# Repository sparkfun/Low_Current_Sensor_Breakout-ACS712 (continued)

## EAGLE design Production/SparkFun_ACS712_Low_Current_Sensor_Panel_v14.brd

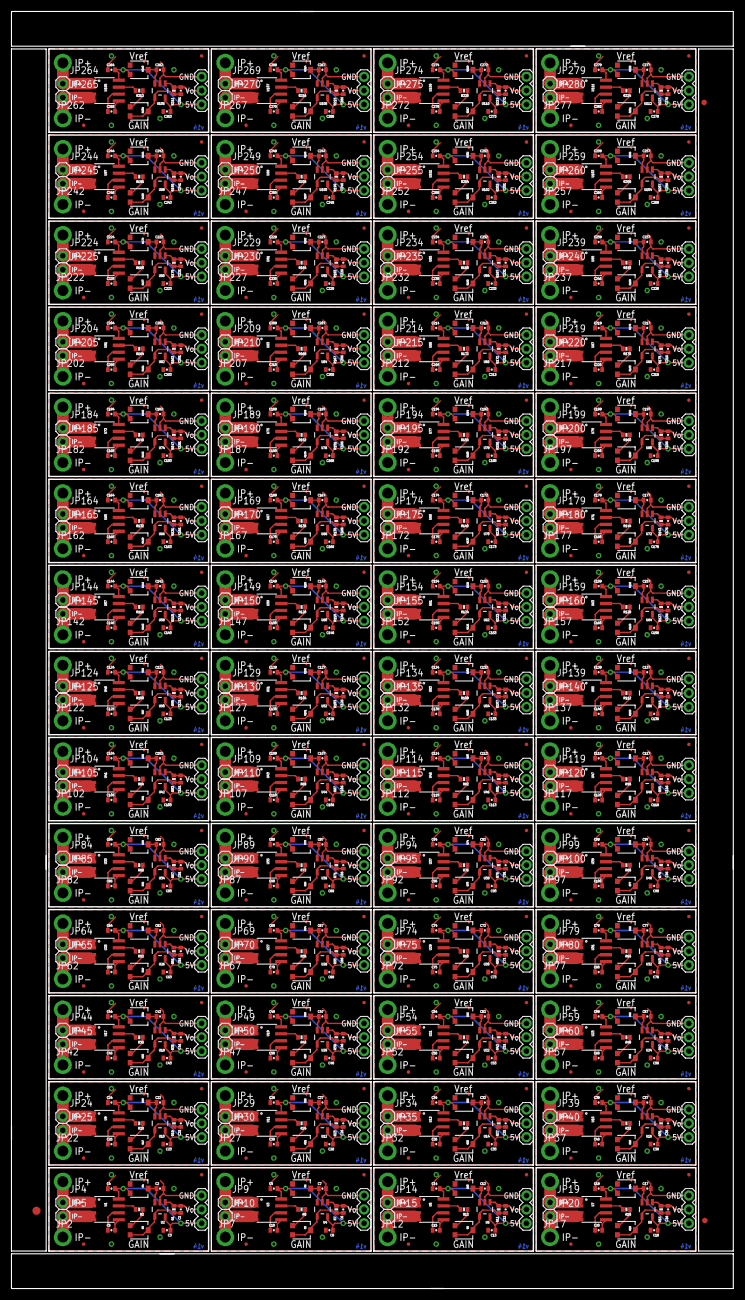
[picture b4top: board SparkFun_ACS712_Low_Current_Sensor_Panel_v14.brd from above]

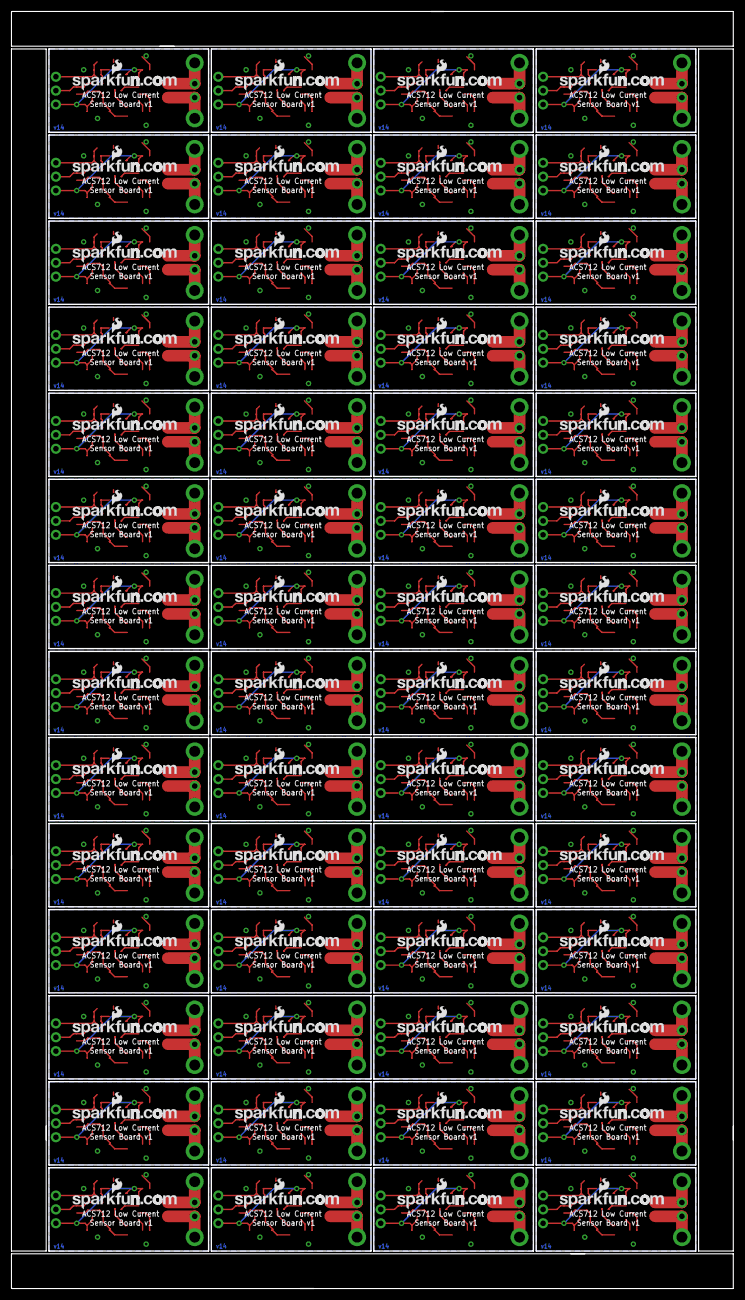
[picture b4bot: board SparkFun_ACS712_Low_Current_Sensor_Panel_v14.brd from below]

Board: 2 copper layers, 132.0 x 233.6 mm, 1067 parts (56 on the bottom side), 560 nets.

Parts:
C1, C2, C3, C4, C6, C7, C8, C9, C11, C12, C13, C14, C16, C17, C18, C19, C21, C22, C23, C24, C26, C27, C28, C29, C31, C32, C33, C34, C36, C37, C38, C39, C41, C42, C43, C44, C46, C47, C48, C49, C51, C52, C53, C54, C56, C57, C58, C59, C61, C62, C63, C64, C66, C67, C68, C69, C71, C72, C73, C74, C76, C77, C78, C79, C81, C82, C83, C84, C86, C87, C88, C89, C91, C92, C93, C94, C96, C97, C98, C99, C101, C102, C103, C104, C106, C107, C108, C109, C111, C112, C113, C114, C116, C117, C118, C119, C121, C122, C123, C124, C126, C127, C128, C129, C131, C132, C133, C134, C136, C137, C138, C139, C141, C142, C143, C144, C146, C147, C148, C149, C151, C152, C153, C154, C156, C157, C158, C159, C161, C162, C163, C164, C166, C167, C168, C169, C171, C172, C173, C174, C176, C177, C178, C179, C181, C182, C183, C184, C186, C187, C188, C189, C191, C192, C193, C194, C196, C197, C198, C199, C201, C202, C203, C204, C206, C207, C208, C209, C211, C212, C213, C214, C216, C217, C218, C219, C221, C222, C223, C224, C226, C227, C228, C229, C231, C232, C233, C234, C236, C237, C238, C239, C241, C242, C243, C244, C246, C247, C248, C249, C251, C252, C253, C254, C256, C257, C258, C259, C261, C262, C263, C264, C266, C267, C268, C269, C271, C272, C273, C274, C276, C277, C278, C279: 0.1uF; 0402-CAP
C5, C10, C15, C20, C25, C30, C35, C40, C45, C50, C55, C60, C65, C70, C75, C80, C85, C90, C95, C100, C105, C110, C115, C120, C125, C130, C135, C140, C145, C150, C155, C160, C165, C170, C175, C180, C185, C190, C195, C200, C205, C210, C215, C220, C225, C230, C235, C240, C245, C250, C255, C260, C265, C270, C275, C280: 1nF; 0402-CAP
E$1: FIDUCIAL-1.5X3
E$5, E$7: FIDUCIAL-1X2
JP1, JP2, JP6, JP7, JP11, JP12, JP16, JP17, JP21, JP22, JP26, JP27, JP31, JP32, JP36, JP37, JP41, JP42, JP46, JP47, JP51, JP52, JP56, JP57, JP61, JP62, JP66, JP67, JP71, JP72, JP76, JP77, JP81, JP82, JP86, JP87, JP91, JP92, JP96, JP97, JP101, JP102, JP106, JP107, JP111, JP112, JP116, JP117, JP121, JP122, JP126, JP127, JP131, JP132, JP136, JP137, JP141, JP142, JP146, JP147, JP151, JP152, JP156, JP157, JP161, JP162, JP166, JP167, JP171, JP172, JP176, JP177, JP181, JP182, JP186, JP187, JP191, JP192, JP196, JP197, JP201, JP202, JP206, JP207, JP211, JP212, JP216, JP217, JP221, JP222, JP226, JP227, JP231, JP232, JP236, JP237, JP241, JP242, JP246, JP247, JP251, JP252, JP256, JP257, JP261, JP262, JP266, JP267, JP271, JP272, JP276, JP277: M01PTH_2MM; 1X01_2MM
JP3, JP8, JP13, JP18, JP23, JP28, JP33, JP38, JP43, JP48, JP53, JP58, JP63, JP68, JP73, JP78, JP83, JP88, JP93, JP98, JP103, JP108, JP113, JP118, JP123, JP128, JP133, JP138, JP143, JP148, JP153, JP158, JP163, JP168, JP173, JP178, JP183, JP188, JP193, JP198, JP203, JP208, JP213, JP218, JP223, JP228, JP233, JP238, JP243, JP248, JP253, JP258, JP263, JP268, JP273, JP278: 1X03
JP4, JP5, JP9, JP10, JP14, JP15, JP19, JP20, JP24, JP25, JP29, JP30, JP34, JP35, JP39, JP40, JP44, JP45, JP49, JP50, JP54, JP55, JP59, JP60, JP64, JP65, JP69, JP70, JP74, JP75, JP79, JP80, JP84, JP85, JP89, JP90, JP94, JP95, JP99, JP100, JP104, JP105, JP109, JP110, JP114, JP115, JP119, JP120, JP124, JP125, JP129, JP130, JP134, JP135, JP139, JP140, JP144, JP145, JP149, JP150, JP154, JP155, JP159, JP160, JP164, JP165, JP169, JP170, JP174, JP175, JP179, JP180, JP184, JP185, JP189, JP190, JP194, JP195, JP199, JP200, JP204, JP205, JP209, JP210, JP214, JP215, JP219, JP220, JP224, JP225, JP229, JP230, JP234, JP235, JP239, JP240, JP244, JP245, JP249, JP250, JP254, JP255, JP259, JP260, JP264, JP265, JP269, JP270, JP274, JP275, JP279, JP280: M01PTH; 1X01
R1, R7, R11, R15, R19, R23, R27, R31, R35, R39, R43, R47, R51, R55, R59, R63, R67, R71, R75, R79, R83, R87, R91, R95, R99, R103, R107, R111, R115, R119, R123, R127, R131, R135, R139, R143, R147, R151, R155, R159, R163, R167, R171, R175, R179, R183, R187, R191, R195, R199, R203, R207, R211, R215, R219, R223: 47K; 0402-RES
R2, R8, R12, R16, R20, R24, R28, R32, R36, R40, R44, R48, R52, R56, R60, R64, R68, R72, R76, R80, R84, R88, R92, R96, R100, R104, R108, R112, R116, R120, R124, R128, R132, R136, R140, R144, R148, R152, R156, R160, R164, R168, R172, R176, R180, R184, R188, R192, R196, R200, R204, R208, R212, R216, R220, R224: 1K; 0402-RES
R3, R4, R5, R6, R9, R10, R13, R14, R17, R18, R21, R22, R25, R26, R29, R30, R33, R34, R37, R38, R41, R42, R45, R46, R49, R50, R53, R54, R57, R58, R61, R62, R65, R66, R69, R70, R73, R74, R77, R78, R81, R82, R85, R86, R89, R90, R93, R94, R97, R98, R101, R102, R105, R106, R109, R110, R113, R114, R117, R118, R121, R122, R125, R126, R129, R130, R133, R134, R137, R138, R141, R142, R145, R146, R149, R150, R153, R154, R157, R158, R161, R162, R165, R166, R169, R170, R173, R174, R177, R178, R181, R182, R185, R186, R189, R190, R193, R194, R197, R198, R201, R202, R205, R206, R209, R210, R213, R214, R217, R218, R221, R222: TRIMPOTSMD; TRIMPOT-3MM
U1, U3, U5, U7, U9, U11, U13, U15, U17, U19, U21, U23, U25, U27, U29, U31, U33, U35, U37, U39, U41, U43, U45, U47, U49, U51, U53, U55, U57, U59, U61, U63, U65, U67, U69, U71, U73, U75, U77, U79, U81, U83, U85, U87, U89, U91, U93, U95, U97, U99, U101, U103, U105, U107, U109, U111: ACS712; SO08
U2, U4, U6, U8, U10, U12, U14, U16, U18, U20, U22, U24, U26, U28, U30, U32, U34, U36, U38, U40, U42, U44, U46, U48, U50, U52, U54, U56, U58, U60, U62, U64, U66, U68, U70, U72, U74, U76, U78, U80, U82, U84, U86, U88, U90, U92, U94, U96, U98, U100, U102, U104, U106, U108, U110, U112: OPA344; SOT23-5
U$1, U$3, U$5, U$6, U$8, U$9, U$11, U$12, U$14, U$15, U$17, U$18, U$20, U$21, U$23, U$24, U$26, U$27, U$29, U$30, U$32, U$33, U$35, U$36, U$38, U$39, U$41, U$42, U$44, U$45, U$47, U$48, U$50, U$51, U$53, U$54, U$56, U$57, U$59, U$60, U$62, U$63, U$65, U$66, U$68, U$69, U$71, U$72, U$74, U$75, U$77, U$78, U$80, U$81, U$83, U$84, U$86, U$87, U$89, U$90, U$92, U$93, U$95, U$96, U$98, U$99, U$101, U$102, U$104, U$105, U$107, U$108, U$110, U$111, U$113, U$114, U$116, U$117, U$119, U$120, U$122, U$123, U$125, U$126, U$128, U$129, U$131, U$132, U$134, U$135, U$137, U$138, U$140, U$141, U$143, U$144, U$146, U$147, U$149, U$150, U$152, U$153, U$155, U$156, U$158, U$159, U$161, U$162, U$164, U$165, U$167, U$168: FIDUCIALUFIDUCIAL; MICRO-FIDUCIAL
U$2, U$4, U$7, U$10, U$13, U$16, U$19, U$22, U$25, U$28, U$31, U$34, U$37, U$40, U$43, U$46, U$49, U$52, U$55, U$58, U$61, U$64, U$67, U$70, U$73, U$76, U$79, U$82, U$85, U$88, U$91, U$94, U$97, U$100, U$103, U$106, U$109, U$112, U$115, U$118, U$121, U$124, U$127, U$130, U$133, U$136, U$139, U$142, U$145, U$148, U$151, U$154, U$157, U$160, U$163, U$166: LOGO-SFENEW; SFE-NEW-WEBLOGO

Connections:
5V: C3.1, C4.2, JP3.1, R4.3, U1.8, U2.5
5V1: C8.1, C9.2, JP8.1, R6.3, U3.8, U4.5
5V2: C13.1, C14.2, JP13.1, R10.3, U5.8, U6.5
5V3: C18.1, C19.2, JP18.1, R14.3, U7.8, U8.5
5V4: C23.1, C24.2, JP23.1, R18.3, U9.8, U10.5
5V5: C28.1, C29.2, JP28.1, R22.3, U11.8, U12.5
5V6: C33.1, C34.2, JP33.1, R26.3, U13.8, U14.5
5V7: C38.1, C39.2, JP38.1, R30.3, U15.8, U16.5
5V8: C43.1, C44.2, JP43.1, R34.3, U17.8, U18.5
5V9: C48.1, C49.2, JP48.1, R38.3, U19.8, U20.5
5V10: C53.1, C54.2, JP53.1, R42.3, U21.8, U22.5
5V11: C58.1, C59.2, JP58.1, R46.3, U23.8, U24.5
5V12: C63.1, C64.2, JP63.1, R50.3, U25.8, U26.5
5V13: C68.1, C69.2, JP68.1, R54.3, U27.8, U28.5
5V14: C73.1, C74.2, JP73.1, R58.3, U29.8, U30.5
5V15: C78.1, C79.2, JP78.1, R62.3, U31.8, U32.5
5V16: C83.1, C84.2, JP83.1, R66.3, U33.8, U34.5
5V17: C88.1, C89.2, JP88.1, R70.3, U35.8, U36.5
5V18: C93.1, C94.2, JP93.1, R74.3, U37.8, U38.5
5V19: C98.1, C99.2, JP98.1, R78.3, U39.8, U40.5
5V20: C103.1, C104.2, JP103.1, R82.3, U41.8, U42.5
5V21: C108.1, C109.2, JP108.1, R86.3, U43.8, U44.5
5V22: C113.1, C114.2, JP113.1, R90.3, U45.8, U46.5
5V23: C118.1, C119.2, JP118.1, R94.3, U47.8, U48.5
5V24: C123.1, C124.2, JP123.1, R98.3, U49.8, U50.5
5V25: C128.1, C129.2, JP128.1, R102.3, U51.8, U52.5
5V26: C133.1, C134.2, JP133.1, R106.3, U53.8, U54.5
5V27: C138.1, C139.2, JP138.1, R110.3, U55.8, U56.5
5V28: C143.1, C144.2, JP143.1, R114.3, U57.8, U58.5
5V29: C148.1, C149.2, JP148.1, R118.3, U59.8, U60.5
5V30: C153.1, C154.2, JP153.1, R122.3, U61.8, U62.5
5V31: C158.1, C159.2, JP158.1, R126.3, U63.8, U64.5
5V32: C163.1, C164.2, JP163.1, R130.3, U65.8, U66.5
5V33: C168.1, C169.2, JP168.1, R134.3, U67.8, U68.5
5V34: C173.1, C174.2, JP173.1, R138.3, U69.8, U70.5
5V35: C178.1, C179.2, JP178.1, R142.3, U71.8, U72.5
5V36: C183.1, C184.2, JP183.1, R146.3, U73.8, U74.5
5V37: C188.1, C189.2, JP188.1, R150.3, U75.8, U76.5
5V38: C193.1, C194.2, JP193.1, R154.3, U77.8, U78.5
5V39: C198.1, C199.2, JP198.1, R158.3, U79.8, U80.5
5V40: C203.1, C204.2, JP203.1, R162.3, U81.8, U82.5
5V41: C208.1, C209.2, JP208.1, R166.3, U83.8, U84.5
5V42: C213.1, C214.2, JP213.1, R170.3, U85.8, U86.5
5V43: C218.1, C219.2, JP218.1, R174.3, U87.8, U88.5
5V44: C223.1, C224.2, JP223.1, R178.3, U89.8, U90.5
5V45: C228.1, C229.2, JP228.1, R182.3, U91.8, U92.5
5V46: C233.1, C234.2, JP233.1, R186.3, U93.8, U94.5
5V47: C238.1, C239.2, JP238.1, R190.3, U95.8, U96.5
5V48: C243.1, C244.2, JP243.1, R194.3, U97.8, U98.5
5V49: C248.1, C249.2, JP248.1, R198.3, U99.8, U100.5
5V50: C253.1, C254.2, JP253.1, R202.3, U101.8, U102.5
5V51: C258.1, C259.2, JP258.1, R206.3, U103.8, U104.5
5V52: C263.1, C264.2, JP263.1, R210.3, U105.8, U106.5
5V53: C268.1, C269.2, JP268.1, R214.3, U107.8, U108.5
5V54: C273.1, C274.2, JP273.1, R218.3, U109.8, U110.5
5V55: C278.1, C279.2, JP278.1, R222.3, U111.8, U112.5
GND: C2.2, C3.2, C4.1, C5.2, JP3.3, R4.1, U1.5, U2.2
GND1: C7.2, C8.2, C9.1, C10.2, JP8.3, R6.1, U3.5, U4.2
GND2: C12.2, C13.2, C14.1, C15.2, JP13.3, R10.1, U5.5, U6.2
GND3: C17.2, C18.2, C19.1, C20.2, JP18.3, R14.1, U7.5, U8.2
GND4: C22.2, C23.2, C24.1, C25.2, JP23.3, R18.1, U9.5, U10.2
GND5: C27.2, C28.2, C29.1, C30.2, JP28.3, R22.1, U11.5, U12.2
GND6: C32.2, C33.2, C34.1, C35.2, JP33.3, R26.1, U13.5, U14.2
GND7: C37.2, C38.2, C39.1, C40.2, JP38.3, R30.1, U15.5, U16.2
GND8: C42.2, C43.2, C44.1, C45.2, JP43.3, R34.1, U17.5, U18.2
GND9: C47.2, C48.2, C49.1, C50.2, JP48.3, R38.1, U19.5, U20.2
GND10: C52.2, C53.2, C54.1, C55.2, JP53.3, R42.1, U21.5, U22.2
GND11: C57.2, C58.2, C59.1, C60.2, JP58.3, R46.1, U23.5, U24.2
GND12: C62.2, C63.2, C64.1, C65.2, JP63.3, R50.1, U25.5, U26.2
GND13: C67.2, C68.2, C69.1, C70.2, JP68.3, R54.1, U27.5, U28.2
GND14: C72.2, C73.2, C74.1, C75.2, JP73.3, R58.1, U29.5, U30.2
GND15: C77.2, C78.2, C79.1, C80.2, JP78.3, R62.1, U31.5, U32.2
GND16: C82.2, C83.2, C84.1, C85.2, JP83.3, R66.1, U33.5, U34.2
GND17: C87.2, C88.2, C89.1, C90.2, JP88.3, R70.1, U35.5, U36.2
GND18: C92.2, C93.2, C94.1, C95.2, JP93.3, R74.1, U37.5, U38.2
GND19: C97.2, C98.2, C99.1, C100.2, JP98.3, R78.1, U39.5, U40.2
GND20: C102.2, C103.2, C104.1, C105.2, JP103.3, R82.1, U41.5, U42.2
GND21: C107.2, C108.2, C109.1, C110.2, JP108.3, R86.1, U43.5, U44.2
GND22: C112.2, C113.2, C114.1, C115.2, JP113.3, R90.1, U45.5, U46.2
GND23: C117.2, C118.2, C119.1, C120.2, JP118.3, R94.1, U47.5, U48.2
GND24: C122.2, C123.2, C124.1, C125.2, JP123.3, R98.1, U49.5, U50.2
GND25: C127.2, C128.2, C129.1, C130.2, JP128.3, R102.1, U51.5, U52.2
GND26: C132.2, C133.2, C134.1, C135.2, JP133.3, R106.1, U53.5, U54.2
GND27: C137.2, C138.2, C139.1, C140.2, JP138.3, R110.1, U55.5, U56.2
GND28: C142.2, C143.2, C144.1, C145.2, JP143.3, R114.1, U57.5, U58.2
GND29: C147.2, C148.2, C149.1, C150.2, JP148.3, R118.1, U59.5, U60.2
GND30: C152.2, C153.2, C154.1, C155.2, JP153.3, R122.1, U61.5, U62.2
GND31: C157.2, C158.2, C159.1, C160.2, JP158.3, R126.1, U63.5, U64.2
GND32: C162.2, C163.2, C164.1, C165.2, JP163.3, R130.1, U65.5, U66.2
GND33: C167.2, C168.2, C169.1, C170.2, JP168.3, R134.1, U67.5, U68.2
GND34: C172.2, C173.2, C174.1, C175.2, JP173.3, R138.1, U69.5, U70.2
GND35: C177.2, C178.2, C179.1, C180.2, JP178.3, R142.1, U71.5, U72.2
GND36: C182.2, C183.2, C184.1, C185.2, JP183.3, R146.1, U73.5, U74.2
GND37: C187.2, C188.2, C189.1, C190.2, JP188.3, R150.1, U75.5, U76.2
GND38: C192.2, C193.2, C194.1, C195.2, JP193.3, R154.1, U77.5, U78.2
GND39: C197.2, C198.2, C199.1, C200.2, JP198.3, R158.1, U79.5, U80.2
GND40: C202.2, C203.2, C204.1, C205.2, JP203.3, R162.1, U81.5, U82.2
GND41: C207.2, C208.2, C209.1, C210.2, JP208.3, R166.1, U83.5, U84.2
GND42: C212.2, C213.2, C214.1, C215.2, JP213.3, R170.1, U85.5, U86.2
GND43: C217.2, C218.2, C219.1, C220.2, JP218.3, R174.1, U87.5, U88.2
GND44: C222.2, C223.2, C224.1, C225.2, JP223.3, R178.1, U89.5, U90.2
GND45: C227.2, C228.2, C229.1, C230.2, JP228.3, R182.1, U91.5, U92.2
GND46: C232.2, C233.2, C234.1, C235.2, JP233.3, R186.1, U93.5, U94.2
GND47: C237.2, C238.2, C239.1, C240.2, JP238.3, R190.1, U95.5, U96.2
GND48: C242.2, C243.2, C244.1, C245.2, JP243.3, R194.1, U97.5, U98.2
GND49: C247.2, C248.2, C249.1, C250.2, JP248.3, R198.1, U99.5, U100.2
GND50: C252.2, C253.2, C254.1, C255.2, JP253.3, R202.1, U101.5, U102.2
GND51: C257.2, C258.2, C259.1, C260.2, JP258.3, R206.1, U103.5, U104.2
GND52: C262.2, C263.2, C264.1, C265.2, JP263.3, R210.1, U105.5, U106.2
GND53: C267.2, C268.2, C269.1, C270.2, JP268.3, R214.1, U107.5, U108.2
GND54: C272.2, C273.2, C274.1, C275.2, JP273.3, R218.1, U109.5, U110.2
GND55: C277.2, C278.2, C279.1, C280.2, JP278.3, R222.1, U111.5, U112.2
IP+: JP1.1, JP4.1, U1.1, U1.2
IP+1: JP6.1, JP9.1, U3.1, U3.2
IP+2: JP11.1, JP14.1, U5.1, U5.2
IP+3: JP16.1, JP19.1, U7.1, U7.2
IP+4: JP21.1, JP24.1, U9.1, U9.2
IP+5: JP26.1, JP29.1, U11.1, U11.2
IP+6: JP31.1, JP34.1, U13.1, U13.2
IP+7: JP36.1, JP39.1, U15.1, U15.2
IP+8: JP41.1, JP44.1, U17.1, U17.2
IP+9: JP46.1, JP49.1, U19.1, U19.2
IP+10: JP51.1, JP54.1, U21.1, U21.2
IP+11: JP56.1, JP59.1, U23.1, U23.2
IP+12: JP61.1, JP64.1, U25.1, U25.2
IP+13: JP66.1, JP69.1, U27.1, U27.2
IP+14: JP71.1, JP74.1, U29.1, U29.2
IP+15: JP76.1, JP79.1, U31.1, U31.2
IP+16: JP81.1, JP84.1, U33.1, U33.2
IP+17: JP86.1, JP89.1, U35.1, U35.2
IP+18: JP91.1, JP94.1, U37.1, U37.2
IP+19: JP96.1, JP99.1, U39.1, U39.2
IP+20: JP101.1, JP104.1, U41.1, U41.2
IP+21: JP106.1, JP109.1, U43.1, U43.2
IP+22: JP111.1, JP114.1, U45.1, U45.2
IP+23: JP116.1, JP119.1, U47.1, U47.2
IP+24: JP121.1, JP124.1, U49.1, U49.2
IP+25: JP126.1, JP129.1, U51.1, U51.2
IP+26: JP131.1, JP134.1, U53.1, U53.2
IP+27: JP136.1, JP139.1, U55.1, U55.2
IP+28: JP141.1, JP144.1, U57.1, U57.2
IP+29: JP146.1, JP149.1, U59.1, U59.2
IP+30: JP151.1, JP154.1, U61.1, U61.2
IP+31: JP156.1, JP159.1, U63.1, U63.2
IP+32: JP161.1, JP164.1, U65.1, U65.2
IP+33: JP166.1, JP169.1, U67.1, U67.2
IP+34: JP171.1, JP174.1, U69.1, U69.2
IP+35: JP176.1, JP179.1, U71.1, U71.2
IP+36: JP181.1, JP184.1, U73.1, U73.2
IP+37: JP186.1, JP189.1, U75.1, U75.2
IP+38: JP191.1, JP194.1, U77.1, U77.2
IP+39: JP196.1, JP199.1, U79.1, U79.2
IP+40: JP201.1, JP204.1, U81.1, U81.2
IP+41: JP206.1, JP209.1, U83.1, U83.2
IP+42: JP211.1, JP214.1, U85.1, U85.2
IP+43: JP216.1, JP219.1, U87.1, U87.2
IP+44: JP221.1, JP224.1, U89.1, U89.2
IP+45: JP226.1, JP229.1, U91.1, U91.2
IP+46: JP231.1, JP234.1, U93.1, U93.2
IP+47: JP236.1, JP239.1, U95.1, U95.2
IP+48: JP241.1, JP244.1, U97.1, U97.2
IP+49: JP246.1, JP249.1, U99.1, U99.2
IP+50: JP251.1, JP254.1, U101.1, U101.2
IP+51: JP256.1, JP259.1, U103.1, U103.2
IP+52: JP261.1, JP264.1, U105.1, U105.2
IP+53: JP266.1, JP269.1, U107.1, U107.2
IP+54: JP271.1, JP274.1, U109.1, U109.2
IP+55: JP276.1, JP279.1, U111.1, U111.2
IP-: JP2.1, JP5.1, U1.3, U1.4
IP-1: JP7.1, JP10.1, U3.3, U3.4
IP-2: JP12.1, JP15.1, U5.3, U5.4
IP-3: JP17.1, JP20.1, U7.3, U7.4
IP-4: JP22.1, JP25.1, U9.3, U9.4
IP-5: JP27.1, JP30.1, U11.3, U11.4
IP-6: JP32.1, JP35.1, U13.3, U13.4
IP-7: JP37.1, JP40.1, U15.3, U15.4
IP-8: JP42.1, JP45.1, U17.3, U17.4
IP-9: JP47.1, JP50.1, U19.3, U19.4
IP-10: JP52.1, JP55.1, U21.3, U21.4
IP-11: JP57.1, JP60.1, U23.3, U23.4
IP-12: JP62.1, JP65.1, U25.3, U25.4
IP-13: JP67.1, JP70.1, U27.3, U27.4
IP-14: JP72.1, JP75.1, U29.3, U29.4
IP-15: JP77.1, JP80.1, U31.3, U31.4
IP-16: JP82.1, JP85.1, U33.3, U33.4
IP-17: JP87.1, JP90.1, U35.3, U35.4
IP-18: JP92.1, JP95.1, U37.3, U37.4
IP-19: JP97.1, JP100.1, U39.3, U39.4
IP-20: JP102.1, JP105.1, U41.3, U41.4
IP-21: JP107.1, JP110.1, U43.3, U43.4
IP-22: JP112.1, JP115.1, U45.3, U45.4
IP-23: JP117.1, JP120.1, U47.3, U47.4
IP-24: JP122.1, JP125.1, U49.3, U49.4
IP-25: JP127.1, JP130.1, U51.3, U51.4
IP-26: JP132.1, JP135.1, U53.3, U53.4
IP-27: JP137.1, JP140.1, U55.3, U55.4
IP-28: JP142.1, JP145.1, U57.3, U57.4
IP-29: JP147.1, JP150.1, U59.3, U59.4
IP-30: JP152.1, JP155.1, U61.3, U61.4
IP-31: JP157.1, JP160.1, U63.3, U63.4
IP-32: JP162.1, JP165.1, U65.3, U65.4
IP-33: JP167.1, JP170.1, U67.3, U67.4
IP-34: JP172.1, JP175.1, U69.3, U69.4
IP-35: JP177.1, JP180.1, U71.3, U71.4
IP-36: JP182.1, JP185.1, U73.3, U73.4
IP-37: JP187.1, JP190.1, U75.3, U75.4
IP-38: JP192.1, JP195.1, U77.3, U77.4
IP-39: JP197.1, JP200.1, U79.3, U79.4
IP-40: JP202.1, JP205.1, U81.3, U81.4
IP-41: JP207.1, JP210.1, U83.3, U83.4
IP-42: JP212.1, JP215.1, U85.3, U85.4
IP-43: JP217.1, JP220.1, U87.3, U87.4
IP-44: JP222.1, JP225.1, U89.3, U89.4
IP-45: JP227.1, JP230.1, U91.3, U91.4
IP-46: JP232.1, JP235.1, U93.3, U93.4
IP-47: JP237.1, JP240.1, U95.3, U95.4
IP-48: JP242.1, JP245.1, U97.3, U97.4
IP-49: JP247.1, JP250.1, U99.3, U99.4
IP-50: JP252.1, JP255.1, U101.3, U101.4
IP-51: JP257.1, JP260.1, U103.3, U103.4
IP-52: JP262.1, JP265.1, U105.3, U105.4
IP-53: JP267.1, JP270.1, U107.3, U107.4
IP-54: JP272.1, JP275.1, U109.3, U109.4
IP-55: JP277.1, JP280.1, U111.3, U111.4
unnamed: R8.2, U3.7
unnamed: R5.1, R8.1
unnamed: R2.2, U1.7
unnamed: R2.1, R3.1
unnamed: C1.2, R1.2, R3.2, R3.3, U2.4
unnamed: C2.1, R4.2, U2.3
unnamed: C6.2, R5.2, R5.3, R7.2, U4.4
unnamed: C5.1, U1.6
unnamed: C7.1, R6.2, U4.3
unnamed: C10.1, U3.6
unnamed: R12.2, U5.7
unnamed: R9.1, R12.1
unnamed: C11.2, R9.2, R9.3, R11.2, U6.4
unnamed: C12.1, R10.2, U6.3
unnamed: C15.1, U5.6
unnamed: R16.2, U7.7
unnamed: R13.1, R16.1
unnamed: C16.2, R13.2, R13.3, R15.2, U8.4
unnamed: C17.1, R14.2, U8.3
unnamed: C20.1, U7.6
unnamed: R20.2, U9.7
unnamed: R17.1, R20.1
unnamed: C21.2, R17.2, R17.3, R19.2, U10.4
unnamed: C22.1, R18.2, U10.3
unnamed: C25.1, U9.6
unnamed: R24.2, U11.7
unnamed: R21.1, R24.1
unnamed: C26.2, R21.2, R21.3, R23.2, U12.4
unnamed: C27.1, R22.2, U12.3
unnamed: C30.1, U11.6
unnamed: R28.2, U13.7
unnamed: R25.1, R28.1
unnamed: C31.2, R25.2, R25.3, R27.2, U14.4
unnamed: C32.1, R26.2, U14.3
unnamed: C35.1, U13.6
unnamed: R32.2, U15.7
unnamed: R29.1, R32.1
unnamed: C36.2, R29.2, R29.3, R31.2, U16.4
unnamed: C37.1, R30.2, U16.3
unnamed: C40.1, U15.6
unnamed: R36.2, U17.7
unnamed: R33.1, R36.1
unnamed: C41.2, R33.2, R33.3, R35.2, U18.4
unnamed: C42.1, R34.2, U18.3
unnamed: C45.1, U17.6
unnamed: R40.2, U19.7
unnamed: R37.1, R40.1
unnamed: C46.2, R37.2, R37.3, R39.2, U20.4
unnamed: C47.1, R38.2, U20.3
unnamed: C50.1, U19.6
unnamed: R44.2, U21.7
unnamed: R41.1, R44.1
unnamed: C51.2, R41.2, R41.3, R43.2, U22.4
unnamed: C52.1, R42.2, U22.3
unnamed: C55.1, U21.6
unnamed: R48.2, U23.7
unnamed: R45.1, R48.1
unnamed: C56.2, R45.2, R45.3, R47.2, U24.4
unnamed: C57.1, R46.2, U24.3
unnamed: C60.1, U23.6
unnamed: R52.2, U25.7
unnamed: R49.1, R52.1
unnamed: C61.2, R49.2, R49.3, R51.2, U26.4
unnamed: C62.1, R50.2, U26.3
unnamed: C65.1, U25.6
unnamed: R56.2, U27.7
unnamed: R53.1, R56.1
unnamed: C66.2, R53.2, R53.3, R55.2, U28.4
unnamed: C67.1, R54.2, U28.3
unnamed: C70.1, U27.6
unnamed: R60.2, U29.7
unnamed: R57.1, R60.1
unnamed: C71.2, R57.2, R57.3, R59.2, U30.4
unnamed: C72.1, R58.2, U30.3
unnamed: C75.1, U29.6
unnamed: R64.2, U31.7
unnamed: R61.1, R64.1
unnamed: C76.2, R61.2, R61.3, R63.2, U32.4
unnamed: C77.1, R62.2, U32.3
unnamed: C80.1, U31.6
unnamed: R68.2, U33.7
unnamed: R65.1, R68.1
unnamed: C81.2, R65.2, R65.3, R67.2, U34.4
unnamed: C82.1, R66.2, U34.3
unnamed: C85.1, U33.6
unnamed: R72.2, U35.7
unnamed: R69.1, R72.1
unnamed: C86.2, R69.2, R69.3, R71.2, U36.4
unnamed: C87.1, R70.2, U36.3
unnamed: C90.1, U35.6
unnamed: R76.2, U37.7
unnamed: R73.1, R76.1
unnamed: C91.2, R73.2, R73.3, R75.2, U38.4
unnamed: C92.1, R74.2, U38.3
unnamed: C95.1, U37.6
unnamed: R80.2, U39.7
unnamed: R77.1, R80.1
unnamed: C96.2, R77.2, R77.3, R79.2, U40.4
unnamed: C97.1, R78.2, U40.3
unnamed: C100.1, U39.6
unnamed: R84.2, U41.7
unnamed: R81.1, R84.1
unnamed: C101.2, R81.2, R81.3, R83.2, U42.4
unnamed: C102.1, R82.2, U42.3
unnamed: C105.1, U41.6
unnamed: R88.2, U43.7
unnamed: R85.1, R88.1
unnamed: C106.2, R85.2, R85.3, R87.2, U44.4
unnamed: C107.1, R86.2, U44.3
unnamed: C110.1, U43.6
unnamed: R92.2, U45.7
unnamed: R89.1, R92.1
unnamed: C111.2, R89.2, R89.3, R91.2, U46.4
unnamed: C112.1, R90.2, U46.3
unnamed: C115.1, U45.6
unnamed: R96.2, U47.7
unnamed: R93.1, R96.1
unnamed: C116.2, R93.2, R93.3, R95.2, U48.4
unnamed: C117.1, R94.2, U48.3
unnamed: C120.1, U47.6
unnamed: R100.2, U49.7
unnamed: R97.1, R100.1
unnamed: C121.2, R97.2, R97.3, R99.2, U50.4
unnamed: C122.1, R98.2, U50.3
unnamed: C125.1, U49.6
unnamed: R104.2, U51.7
unnamed: R101.1, R104.1
unnamed: C126.2, R101.2, R101.3, R103.2, U52.4
unnamed: C127.1, R102.2, U52.3
unnamed: C130.1, U51.6
unnamed: R108.2, U53.7
unnamed: R105.1, R108.1
unnamed: C131.2, R105.2, R105.3, R107.2, U54.4
unnamed: C132.1, R106.2, U54.3
unnamed: C135.1, U53.6
unnamed: R112.2, U55.7
unnamed: R109.1, R112.1
unnamed: C136.2, R109.2, R109.3, R111.2, U56.4
unnamed: C137.1, R110.2, U56.3
unnamed: C140.1, U55.6
unnamed: R116.2, U57.7
unnamed: R113.1, R116.1
unnamed: C141.2, R113.2, R113.3, R115.2, U58.4
unnamed: C142.1, R114.2, U58.3
unnamed: C145.1, U57.6
unnamed: R120.2, U59.7
unnamed: R117.1, R120.1
unnamed: C146.2, R117.2, R117.3, R119.2, U60.4
unnamed: C147.1, R118.2, U60.3
unnamed: C150.1, U59.6
unnamed: R124.2, U61.7
unnamed: R121.1, R124.1
unnamed: C151.2, R121.2, R121.3, R123.2, U62.4
unnamed: C152.1, R122.2, U62.3
unnamed: C155.1, U61.6
unnamed: R128.2, U63.7
unnamed: R125.1, R128.1
unnamed: C156.2, R125.2, R125.3, R127.2, U64.4
unnamed: C157.1, R126.2, U64.3
unnamed: C160.1, U63.6
unnamed: R132.2, U65.7
unnamed: R129.1, R132.1
unnamed: C161.2, R129.2, R129.3, R131.2, U66.4
unnamed: C162.1, R130.2, U66.3
unnamed: C165.1, U65.6
unnamed: R136.2, U67.7
unnamed: R133.1, R136.1
unnamed: C166.2, R133.2, R133.3, R135.2, U68.4
unnamed: C167.1, R134.2, U68.3
unnamed: C170.1, U67.6
unnamed: R140.2, U69.7
unnamed: R137.1, R140.1
unnamed: C171.2, R137.2, R137.3, R139.2, U70.4
unnamed: C172.1, R138.2, U70.3
unnamed: C175.1, U69.6
unnamed: R144.2, U71.7
unnamed: R141.1, R144.1
unnamed: C176.2, R141.2, R141.3, R143.2, U72.4
unnamed: C177.1, R142.2, U72.3
unnamed: C180.1, U71.6
unnamed: R148.2, U73.7
unnamed: R145.1, R148.1
unnamed: C181.2, R145.2, R145.3, R147.2, U74.4
unnamed: C182.1, R146.2, U74.3
unnamed: C185.1, U73.6
unnamed: R152.2, U75.7
unnamed: R149.1, R152.1
unnamed: C186.2, R149.2, R149.3, R151.2, U76.4
unnamed: C187.1, R150.2, U76.3
unnamed: C190.1, U75.6
unnamed: R156.2, U77.7
unnamed: R153.1, R156.1
unnamed: C191.2, R153.2, R153.3, R155.2, U78.4
unnamed: C192.1, R154.2, U78.3
unnamed: C195.1, U77.6
unnamed: R160.2, U79.7
unnamed: R157.1, R160.1
unnamed: C196.2, R157.2, R157.3, R159.2, U80.4
unnamed: C197.1, R158.2, U80.3
unnamed: C200.1, U79.6
unnamed: R164.2, U81.7
unnamed: R161.1, R164.1
unnamed: C201.2, R161.2, R161.3, R163.2, U82.4
unnamed: C202.1, R162.2, U82.3
unnamed: C205.1, U81.6
unnamed: R168.2, U83.7
unnamed: R165.1, R168.1
unnamed: C206.2, R165.2, R165.3, R167.2, U84.4
unnamed: C207.1, R166.2, U84.3
unnamed: C210.1, U83.6
unnamed: R172.2, U85.7
unnamed: R169.1, R172.1
unnamed: C211.2, R169.2, R169.3, R171.2, U86.4
unnamed: C212.1, R170.2, U86.3
unnamed: C215.1, U85.6
unnamed: R176.2, U87.7
unnamed: R173.1, R176.1
unnamed: C216.2, R173.2, R173.3, R175.2, U88.4
unnamed: C217.1, R174.2, U88.3
unnamed: C220.1, U87.6
unnamed: R180.2, U89.7
unnamed: R177.1, R180.1
unnamed: C221.2, R177.2, R177.3, R179.2, U90.4
unnamed: C222.1, R178.2, U90.3
unnamed: C225.1, U89.6
unnamed: R184.2, U91.7
unnamed: R181.1, R184.1
unnamed: C226.2, R181.2, R181.3, R183.2, U92.4
unnamed: C227.1, R182.2, U92.3
unnamed: C230.1, U91.6
unnamed: R188.2, U93.7
unnamed: R185.1, R188.1
unnamed: C231.2, R185.2, R185.3, R187.2, U94.4
unnamed: C232.1, R186.2, U94.3
unnamed: C235.1, U93.6
unnamed: R192.2, U95.7
unnamed: R189.1, R192.1
unnamed: C236.2, R189.2, R189.3, R191.2, U96.4
unnamed: C237.1, R190.2, U96.3
unnamed: C240.1, U95.6
unnamed: R196.2, U97.7
unnamed: R193.1, R196.1
unnamed: C241.2, R193.2, R193.3, R195.2, U98.4
unnamed: C242.1, R194.2, U98.3
unnamed: C245.1, U97.6
unnamed: R200.2, U99.7
unnamed: R197.1, R200.1
unnamed: C246.2, R197.2, R197.3, R199.2, U100.4
unnamed: C247.1, R198.2, U100.3
unnamed: C250.1, U99.6
unnamed: R204.2, U101.7
unnamed: R201.1, R204.1
unnamed: C251.2, R201.2, R201.3, R203.2, U102.4
unnamed: C252.1, R202.2, U102.3
unnamed: C255.1, U101.6
unnamed: R208.2, U103.7
unnamed: R205.1, R208.1
unnamed: C256.2, R205.2, R205.3, R207.2, U104.4
unnamed: C257.1, R206.2, U104.3
unnamed: C260.1, U103.6
unnamed: R212.2, U105.7
unnamed: R209.1, R212.1
unnamed: C261.2, R209.2, R209.3, R211.2, U106.4
unnamed: C262.1, R210.2, U106.3
unnamed: C265.1, U105.6
unnamed: R216.2, U107.7
unnamed: R213.1, R216.1
unnamed: C266.2, R213.2, R213.3, R215.2, U108.4
unnamed: C267.1, R214.2, U108.3
unnamed: C270.1, U107.6
unnamed: R220.2, U109.7
unnamed: R217.1, R220.1
unnamed: C271.2, R217.2, R217.3, R219.2, U110.4
unnamed: C272.1, R218.2, U110.3
unnamed: C275.1, U109.6
unnamed: R224.2, U111.7
unnamed: R221.1, R224.1
unnamed: C276.2, R221.2, R221.3, R223.2, U112.4
unnamed: C277.1, R222.2, U112.3
unnamed: C280.1, U111.6
VO: C1.1, JP3.2, R1.1, U2.1
VO1: C6.1, JP8.2, R7.1, U4.1
VO2: C11.1, JP13.2, R11.1, U6.1
VO3: C16.1, JP18.2, R15.1, U8.1
VO4: C21.1, JP23.2, R19.1, U10.1
VO5: C26.1, JP28.2, R23.1, U12.1
VO6: C31.1, JP33.2, R27.1, U14.1
VO7: C36.1, JP38.2, R31.1, U16.1
VO8: C41.1, JP43.2, R35.1, U18.1
VO9: C46.1, JP48.2, R39.1, U20.1
VO10: C51.1, JP53.2, R43.1, U22.1
VO11: C56.1, JP58.2, R47.1, U24.1
VO12: C61.1, JP63.2, R51.1, U26.1
VO13: C66.1, JP68.2, R55.1, U28.1
VO14: C71.1, JP73.2, R59.1, U30.1
VO15: C76.1, JP78.2, R63.1, U32.1
VO16: C81.1, JP83.2, R67.1, U34.1
VO17: C86.1, JP88.2, R71.1, U36.1
VO18: C91.1, JP93.2, R75.1, U38.1
VO19: C96.1, JP98.2, R79.1, U40.1
VO20: C101.1, JP103.2, R83.1, U42.1
VO21: C106.1, JP108.2, R87.1, U44.1
VO22: C111.1, JP113.2, R91.1, U46.1
VO23: C116.1, JP118.2, R95.1, U48.1
VO24: C121.1, JP123.2, R99.1, U50.1
VO25: C126.1, JP128.2, R103.1, U52.1
VO26: C131.1, JP133.2, R107.1, U54.1
VO27: C136.1, JP138.2, R111.1, U56.1
VO28: C141.1, JP143.2, R115.1, U58.1
VO29: C146.1, JP148.2, R119.1, U60.1
VO30: C151.1, JP153.2, R123.1, U62.1
VO31: C156.1, JP158.2, R127.1, U64.1
VO32: C161.1, JP163.2, R131.1, U66.1
VO33: C166.1, JP168.2, R135.1, U68.1
VO34: C171.1, JP173.2, R139.1, U70.1
VO35: C176.1, JP178.2, R143.1, U72.1
VO36: C181.1, JP183.2, R147.1, U74.1
VO37: C186.1, JP188.2, R151.1, U76.1
VO38: C191.1, JP193.2, R155.1, U78.1
VO39: C196.1, JP198.2, R159.1, U80.1
VO40: C201.1, JP203.2, R163.1, U82.1
VO41: C206.1, JP208.2, R167.1, U84.1
VO42: C211.1, JP213.2, R171.1, U86.1
VO43: C216.1, JP218.2, R175.1, U88.1
VO44: C221.1, JP223.2, R179.1, U90.1
VO45: C226.1, JP228.2, R183.1, U92.1
VO46: C231.1, JP233.2, R187.1, U94.1
VO47: C236.1, JP238.2, R191.1, U96.1
VO48: C241.1, JP243.2, R195.1, U98.1
VO49: C246.1, JP248.2, R199.1, U100.1
VO50: C251.1, JP253.2, R203.1, U102.1
VO51: C256.1, JP258.2, R207.1, U104.1
VO52: C261.1, JP263.2, R211.1, U106.1
VO53: C266.1, JP268.2, R215.1, U108.1
VO54: C271.1, JP273.2, R219.1, U110.1
VO55: C276.1, JP278.2, R223.1, U112.1

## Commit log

2015-03-03 Adding hardware files, updating README
2015-10-29 created new v14 panel
2016-03-01 Updating to proper 100pF cap on C1, removing version number from file names
2016-03-01 Fixing file names
2017-05-16 Adding Arduino example sketch
    George Beckstein created example sketch for this part along with a
    hookup guide. Adding software folder with sketch.
2017-11-27 Rerouting and deletion of original files
2017-11-30 Finalizing v01
    -reduced GND plane to isolate from IP pins
    -swapped all existing 0402 packages to 0603
    -updated trimpot packages
    -added extra copper for large IP traces on bottom copper
    -added bandwidth select jumper
    -swapped in new opamp symbol and package
2017-12-05 Silk and designer details
    -added "designed by" and "revised by" attributes in the SCH and BRD
    -adjusted silk
2017-12-08 finalize for checklist
    -removed oen standoff
    -added 1nf cap
    -moved silk
    -moved header for output
    -added measures
2017-12-11 Changes per v01 checklist
    -moved R1 and C1 closer to the opamp
    -moved silk
    -moved fiducials
2017-12-11 v01 checklist issues
    -added voltage and current ranges
    -labeled JP1 in the SCH
    -reorganized the SCH
2017-12-22 Adjusted the position of a cap
    -C2 Y-axis -.05"
2017-12-29 Adjusted SCH
    -moved standoff and fiducial symbols in schematic
2017-12-29 more post v01 changes
    -adjusted some silk positions
2018-01-31 v01 to v10 changes
    -Removed 3-way jumper and replaced with 2-way
    -changed version in SCH and BRD from v01 to v10
    -adjusted jumper select silk
    -added/adjusted SCH notes to include trimpot guide and jumper guide
2018-01-31 changed name of product so it omits version number
    -removed files with v01 in the name
2018-01-31 default layer changes
2018-01-31 SCH changes
    -added full IC name
    -moved some notes around
2018-02-05 v10 finalization
    -moved some vias for better GND stitching
    -slight silk adjustment
    -changed value of opamp voltage split to allow for similiar spectrum measurment as the previous version. With an output of 220mV more per amp the values of the gain resistors needed to be adjusted to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
2018-02-05 post eng. checklist changes
    -added notes about gain
    -removed uneeded layers
2018-02-08 panel
